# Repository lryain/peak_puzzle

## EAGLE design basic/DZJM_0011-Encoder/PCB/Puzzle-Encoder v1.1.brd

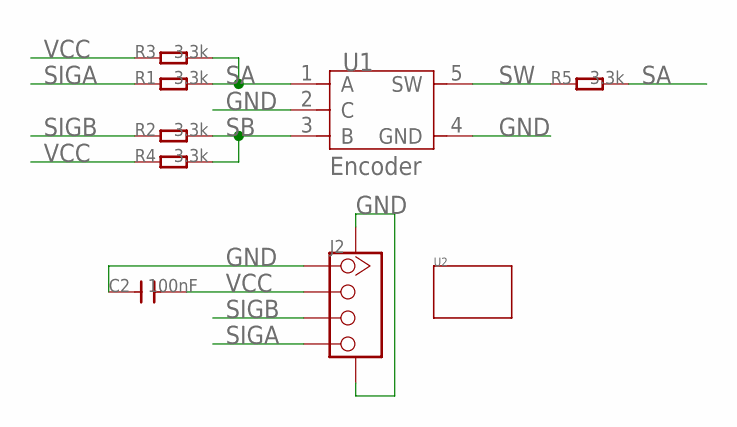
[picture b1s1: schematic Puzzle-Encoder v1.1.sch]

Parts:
C2: 100nF; C0603
J2: TWIG-4P-2.0-SMD-FEMALE-REINFORCE'DD'; 4P-SMD-2.0
R1, R2, R3, R4, R5: 3.3k; R0603
U1: Encoder; 5P-13.75X11.7X6.5H
U2: TWIG'1U'; 1U-DIM-W/-DRILL

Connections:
GND: C2.1, J2.1, J2.SS1, J2.SS2, U1.2 (C), U1.4 (GND)
SA: R1.2, R3.2, R5.2, U1.1 (A)
SB: R2.2, R4.2, U1.3 (B)
SIGA: J2.4, R1.1
SIGB: J2.3, R2.1
SW: R5.1, U1.5 (SW)
VCC: C2.2, J2.2, R3.1, R4.1

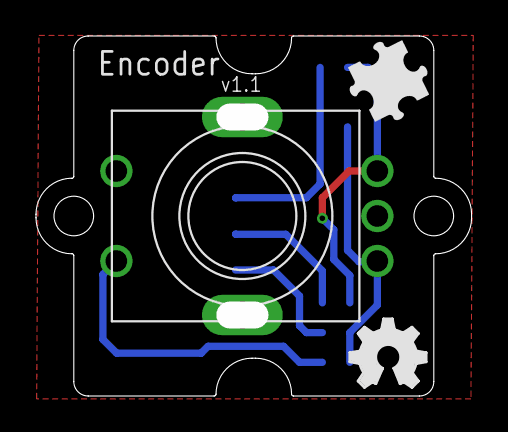
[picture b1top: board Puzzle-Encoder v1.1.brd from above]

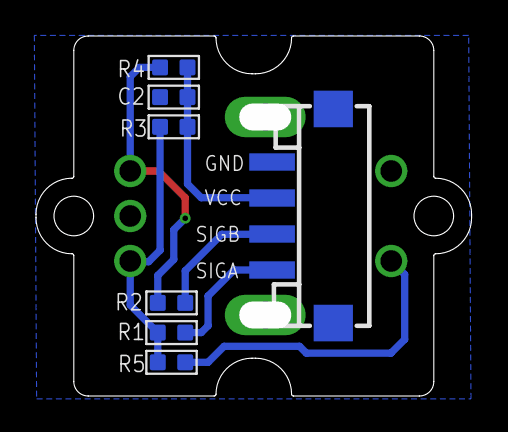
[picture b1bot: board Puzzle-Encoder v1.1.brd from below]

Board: 2 copper layers, 24.2 x 20.0 mm, 11 parts (7 on the bottom side), 7 nets.

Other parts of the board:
U$1: BRICK-LOGO-MIL-0.5
U$2: OSHW_FILLX150_NOTEXT

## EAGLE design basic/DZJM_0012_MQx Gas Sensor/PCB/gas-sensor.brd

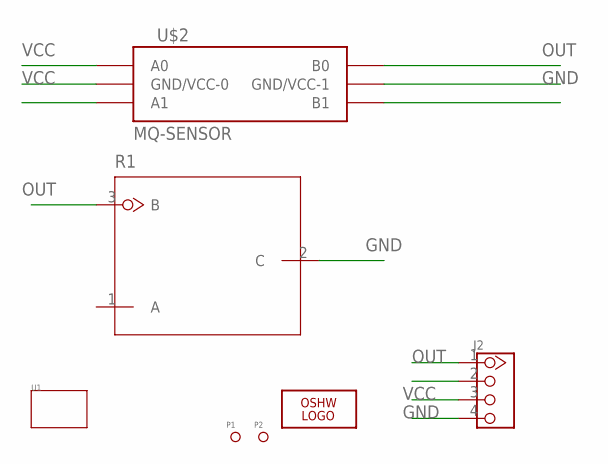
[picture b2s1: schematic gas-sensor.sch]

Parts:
J2: TWIG-2.0-LEADED; 4P-LEADED-2.0
LOGO1: LOGO-OSHW-FILLX0150-NT; OSHW_FILLX150_NOTEXT
P1, P2: PAD-MARK; ROUND-MARK-0.635
R1: DEVICE_RESISTANCE; PACKAGE__RESISTANCE
U1: TWIG-2U; 2U-DIM-W/-DRILL
U$2: MQ-SENSOR; MQ-BASE

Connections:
GND: J2.4, R1.2 (C), U$2.HB (GND/VCC-1)
OUT: J2.1, R1.3 (B), U$2.B1 (B0)
VCC: J2.3, U$2.A1 (A0), U$2.HA (GND/VCC-0)

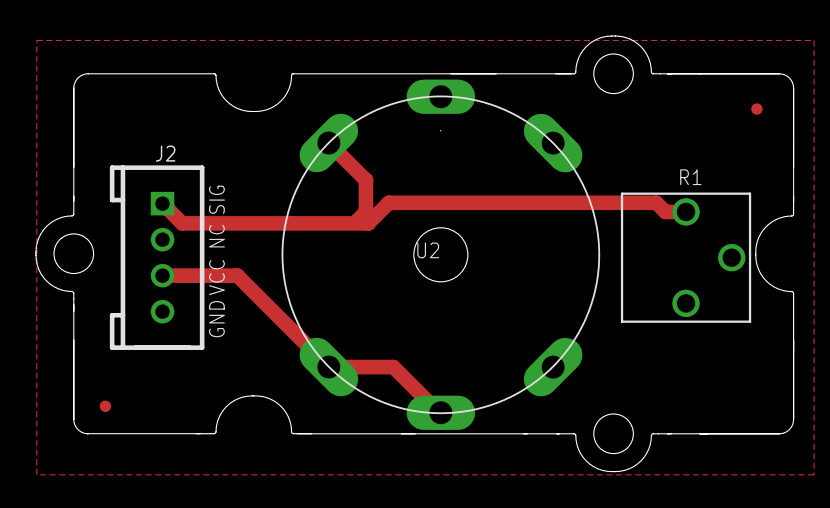
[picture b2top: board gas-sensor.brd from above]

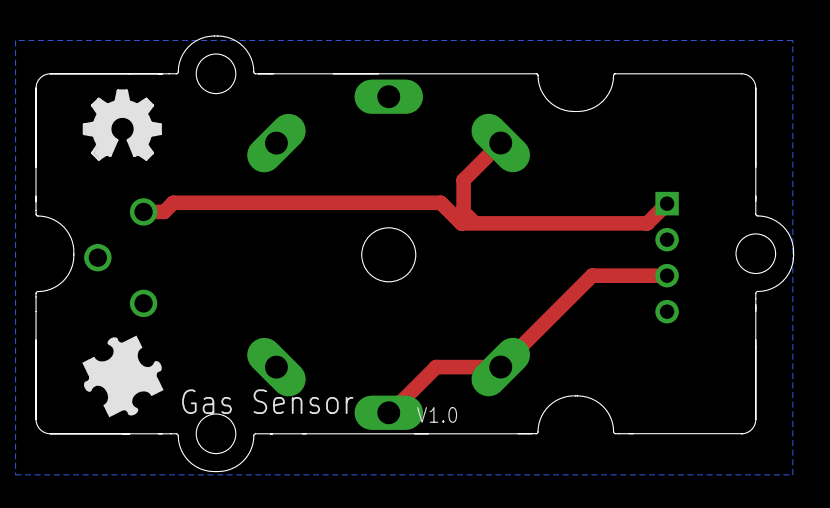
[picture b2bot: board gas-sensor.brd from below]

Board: 2 copper layers, 42.1 x 24.2 mm, 8 parts (2 on the bottom side), 3 nets.

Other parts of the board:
U$1: BRICK-LOGO-MIL-0.5

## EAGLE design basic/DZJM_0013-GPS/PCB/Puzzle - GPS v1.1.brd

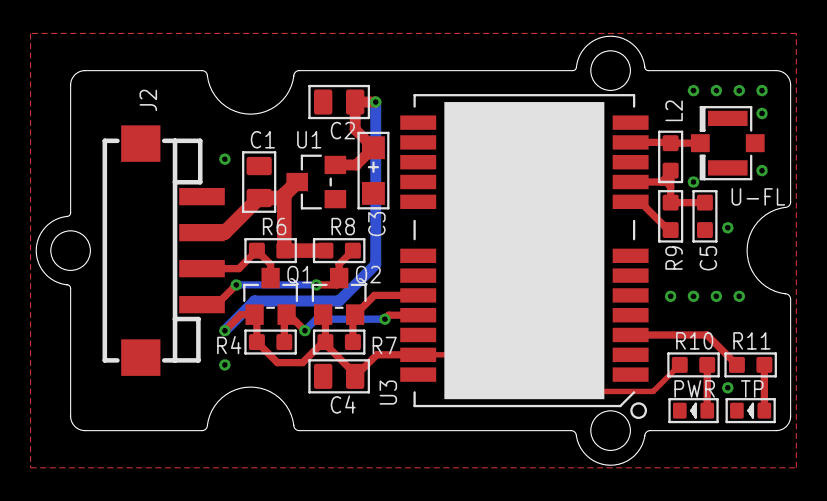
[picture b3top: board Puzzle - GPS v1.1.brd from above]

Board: 2 copper layers, 41.9 x 23.8 mm, 24 parts (1 on the bottom side), 13 nets.

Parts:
C1, C2, C4: 10uF; C0805
C3: DNP; AVX-A
C5: 100nF; C0603
J2: 4P-SMD-2.0
L2: 33nH; L0603
PWR: GREEN; LED-0603
Q1, Q2: BSN20; SOT23
R4, R6, R7, R8: 10k; R0603
R9: 0R; R0603
R10, R11: 330; R0603
TP: DNP; LED-0603
U1: XC6206P332MR-G; SOT23
U3: NEO-6M; 28P-1.1-16.0X12.2
U4: U.FL
U$1: 2U-DIM-W/DRILL
U$2: OSHW_FILLX200_NOTEXT
U$4: BRICK-LOGO-2-B-MIL-0.6

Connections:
3V3: C2.2, C3.+, C4.2, Q1.1, Q2.1, R4.2, R7.2, R10.1, U1.2, U3.23
GND: C1.1, C2.1, C3.-, C4.1, C5.2, J2.4, J2.SS1, J2.SS2, PWR.-, TP.-, U1.1, U3.7, U3.10, U3.12, U3.13, U3.22, U3.24, U4.P$1, U4.P$2
GPS_RX: Q1.2, R4.1, U3.21
GPS_TX: Q2.2, R7.1, U3.20
unnamed: L2.1, U3.11, U4.P$3
unnamed: C5.1, L2.2, R9.1, U3.9
unnamed: PWR.+, R10.2
unnamed: R9.2, U3.8
unnamed: R11.2, TP.+
RX_H: J2.2, Q1.3, R6.1
TP: R11.1, U3.3
TX_H: J2.1, Q2.3, R8.1
VCC: C1.2, J2.3, R6.2, R8.2, U1.3

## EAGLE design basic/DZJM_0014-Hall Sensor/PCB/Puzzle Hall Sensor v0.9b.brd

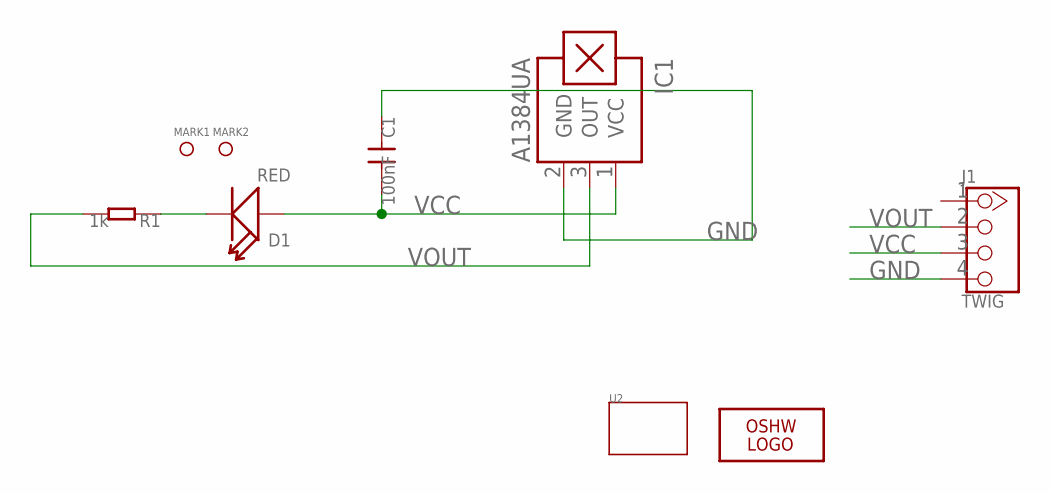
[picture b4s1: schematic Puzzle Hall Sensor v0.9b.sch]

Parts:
C1: 100nF; 0603
D1: RED; D0603
IC1: A1384UA; SIP3-UA
J1: TWIG; 4P-LEADED-2.0
LOGO1: LOGO-OSHW-FILLX0150-NT; OSHW_FILLX150_NOTEXT
MARK1, MARK2: PAD-MARK; ROUND-MARK-0.635
R1: 1k; 0603
U2: TWIG-1U; 1U-DIM-W/-DRILL

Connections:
GND: C1.1, IC1.2 (GND), J1.4
unnamed: D1.-, R1.1
VCC: C1.2, D1.+, IC1.1 (VCC), J1.3
VOUT: IC1.3 (OUT), J1.2, R1.2

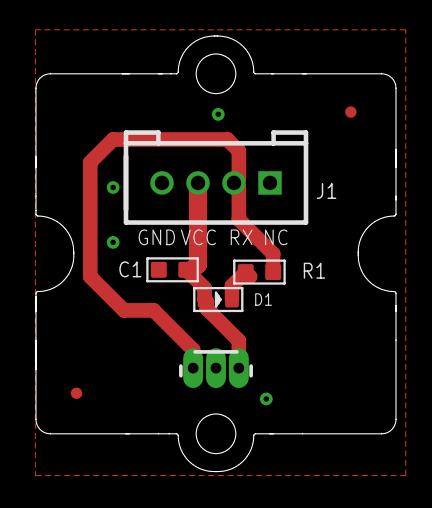
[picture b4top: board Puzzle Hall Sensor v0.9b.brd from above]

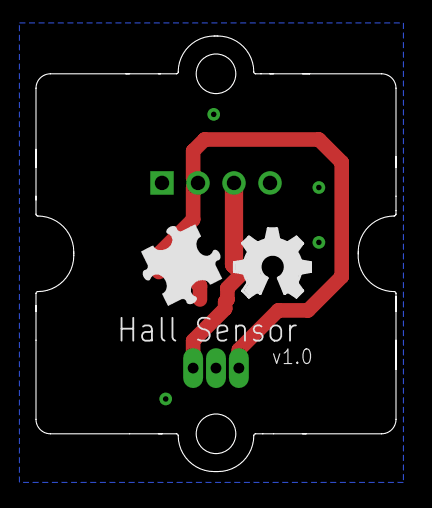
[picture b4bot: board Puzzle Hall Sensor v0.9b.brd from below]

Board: 2 copper layers, 20.0 x 24.2 mm, 10 parts (2 on the bottom side), 4 nets.

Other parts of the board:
U$1: BRICK-LOGO-MIL-0.5

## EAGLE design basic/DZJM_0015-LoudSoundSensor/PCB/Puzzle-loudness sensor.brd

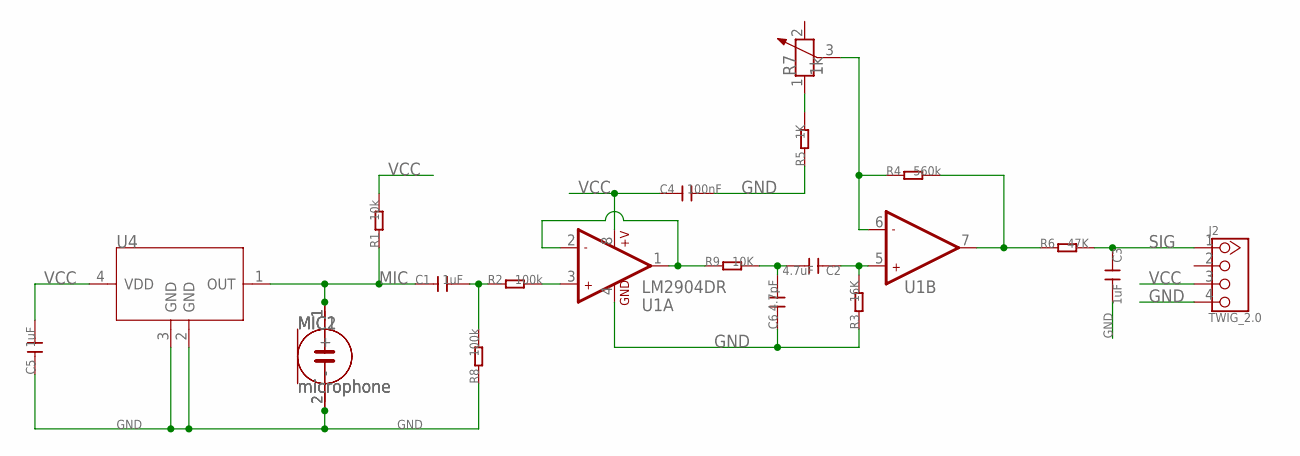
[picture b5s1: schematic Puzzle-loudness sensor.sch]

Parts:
C1, C3, C5: 1uF; C0603
C2: 4.7uF; C0805
C4: 100nF; C0603
C6: 4.7pF; C0603
J2: TWIG_2.0; 2.0_1X4
MIC1, MIC2: microphone; 2P-D8.9MM
R1: 10k; R0603
R2, R8: 100k; R0603
R3: 16K; R0603
R4: 560k; R0603
R5: 1K; R0603
R6: 47K; R0603
R7: 1k; 3P-SQUA-7X6.8
R9: 10K; R0603
U1: LM2904DR; SO08
U4: SENSOR-MULPS4CX; 4P-SMD-2.95X3.76X1.1H

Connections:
GND: C3.2, C4.2, C5.1, C6.1, J2.4, MIC1.2 (-), MIC2.2 (-), R3.1, R5.1, R8.1, U1.4 (GND), U4.2 (GND), U4.3 (GND)
MIC: C1.1, MIC1.1 (+), MIC2.1 (+), R1.1, U4.1 (OUT)
unnamed: R2.2, U1.3 (+IN1)
unnamed: C1.2, R2.1, R8.2
unnamed: R9.1, U1.1 (OUT1), U1.2 (-IN1)
unnamed: C2.1, R3.2, U1.5 (+IN2)
unnamed: R4.1, R7.3, U1.6 (-IN2)
unnamed: R4.2, R6.1, U1.7 (OUT2)
unnamed: R5.2, R7.1
unnamed: C2.2, C6.2, R9.2
SIG: C3.1, J2.1, R6.2
VCC: C4.1, C5.2, J2.3, R1.2, U1.8 (+V), U4.4 (VDD)

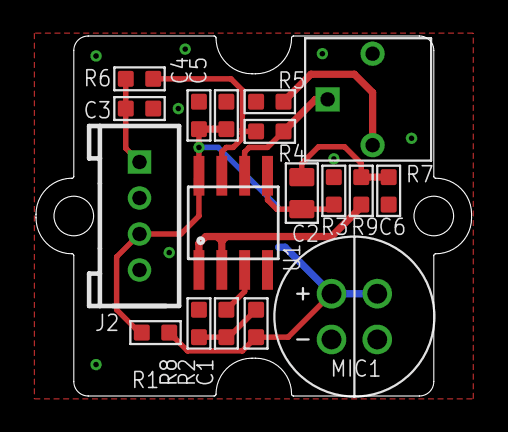
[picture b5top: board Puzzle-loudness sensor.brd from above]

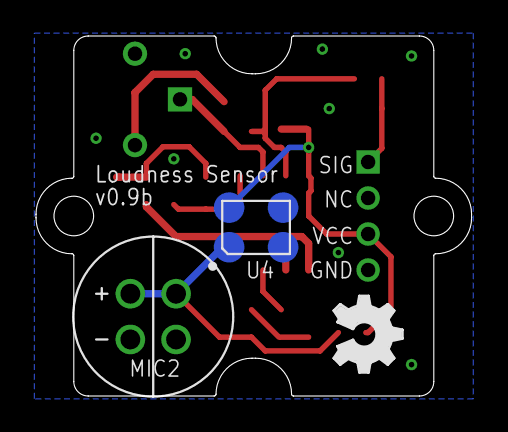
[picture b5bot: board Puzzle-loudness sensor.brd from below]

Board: 2 copper layers, 24.2 x 20.0 mm, 22 parts (3 on the bottom side), 12 nets.

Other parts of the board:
U$1: OSHW_FILLX150_NOTEXT
U$2: 1U-DIM-W/-DRILL

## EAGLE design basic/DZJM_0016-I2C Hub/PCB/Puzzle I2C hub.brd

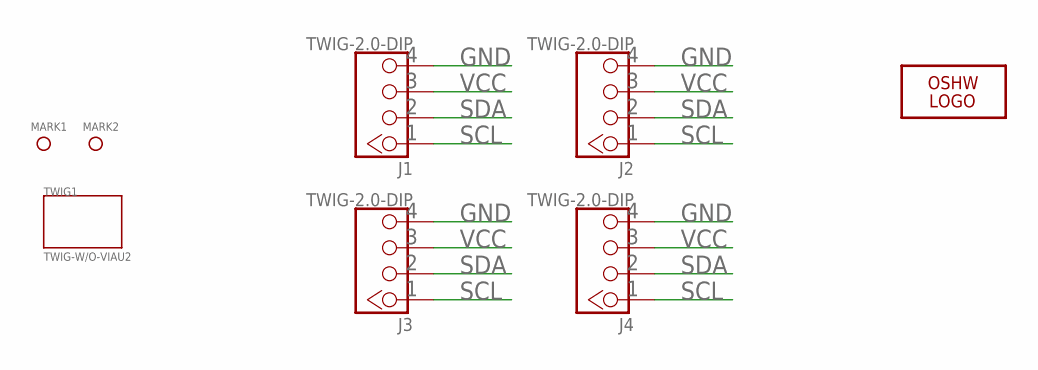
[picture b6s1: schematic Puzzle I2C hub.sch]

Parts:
J1, J2, J3, J4: TWIG-2.0-DIP; 2.0_1X4
LOGO3: LOGO-OSHW-FILLX0150-NT; OSHW_FILLX150_NOTEXT
MARK1, MARK2: PAD-MARK; MARK
TWIG1: TWIG-W/O-VIAU2; U2N

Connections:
GND: J1.4, J2.4, J3.4, J4.4
SCL: J1.1, J2.1, J3.1, J4.1
SDA: J1.2, J2.2, J3.2, J4.2
VCC: J1.3, J2.3, J3.3, J4.3

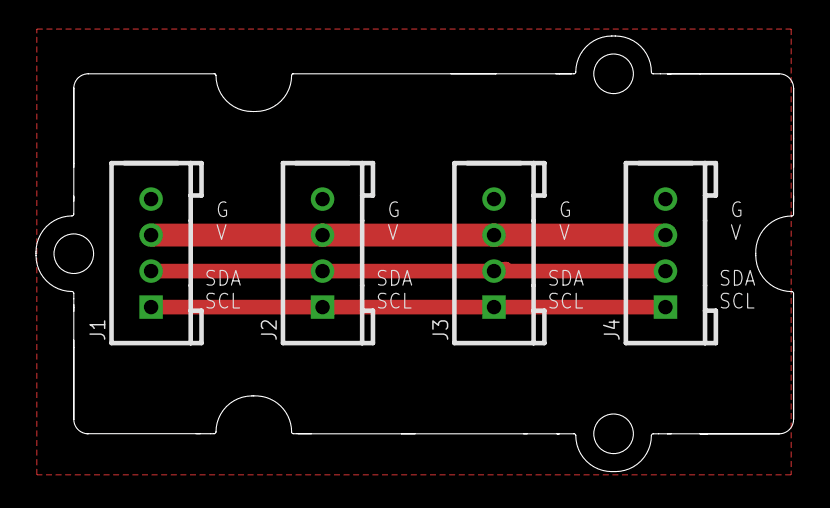
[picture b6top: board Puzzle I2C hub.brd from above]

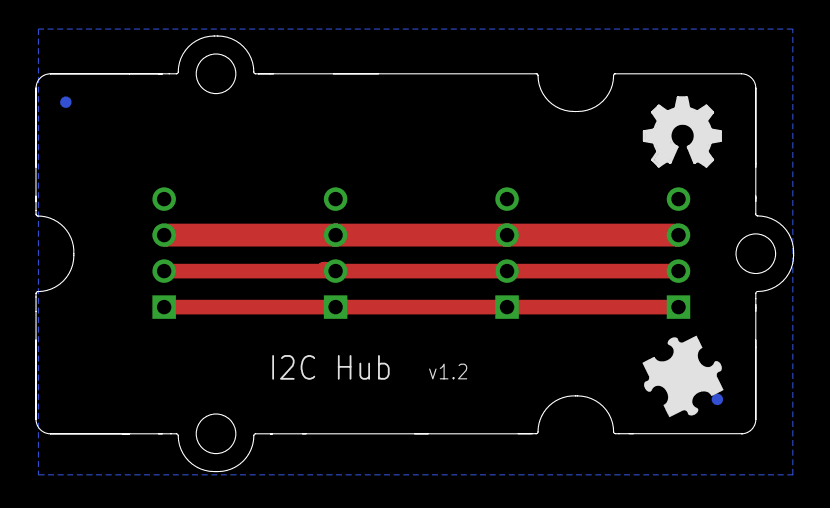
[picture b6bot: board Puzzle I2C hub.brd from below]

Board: 2 copper layers, 42.1 x 24.2 mm, 9 parts (4 on the bottom side), 4 nets.

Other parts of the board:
U$2: BRICK-LOGO-MIL-0.5

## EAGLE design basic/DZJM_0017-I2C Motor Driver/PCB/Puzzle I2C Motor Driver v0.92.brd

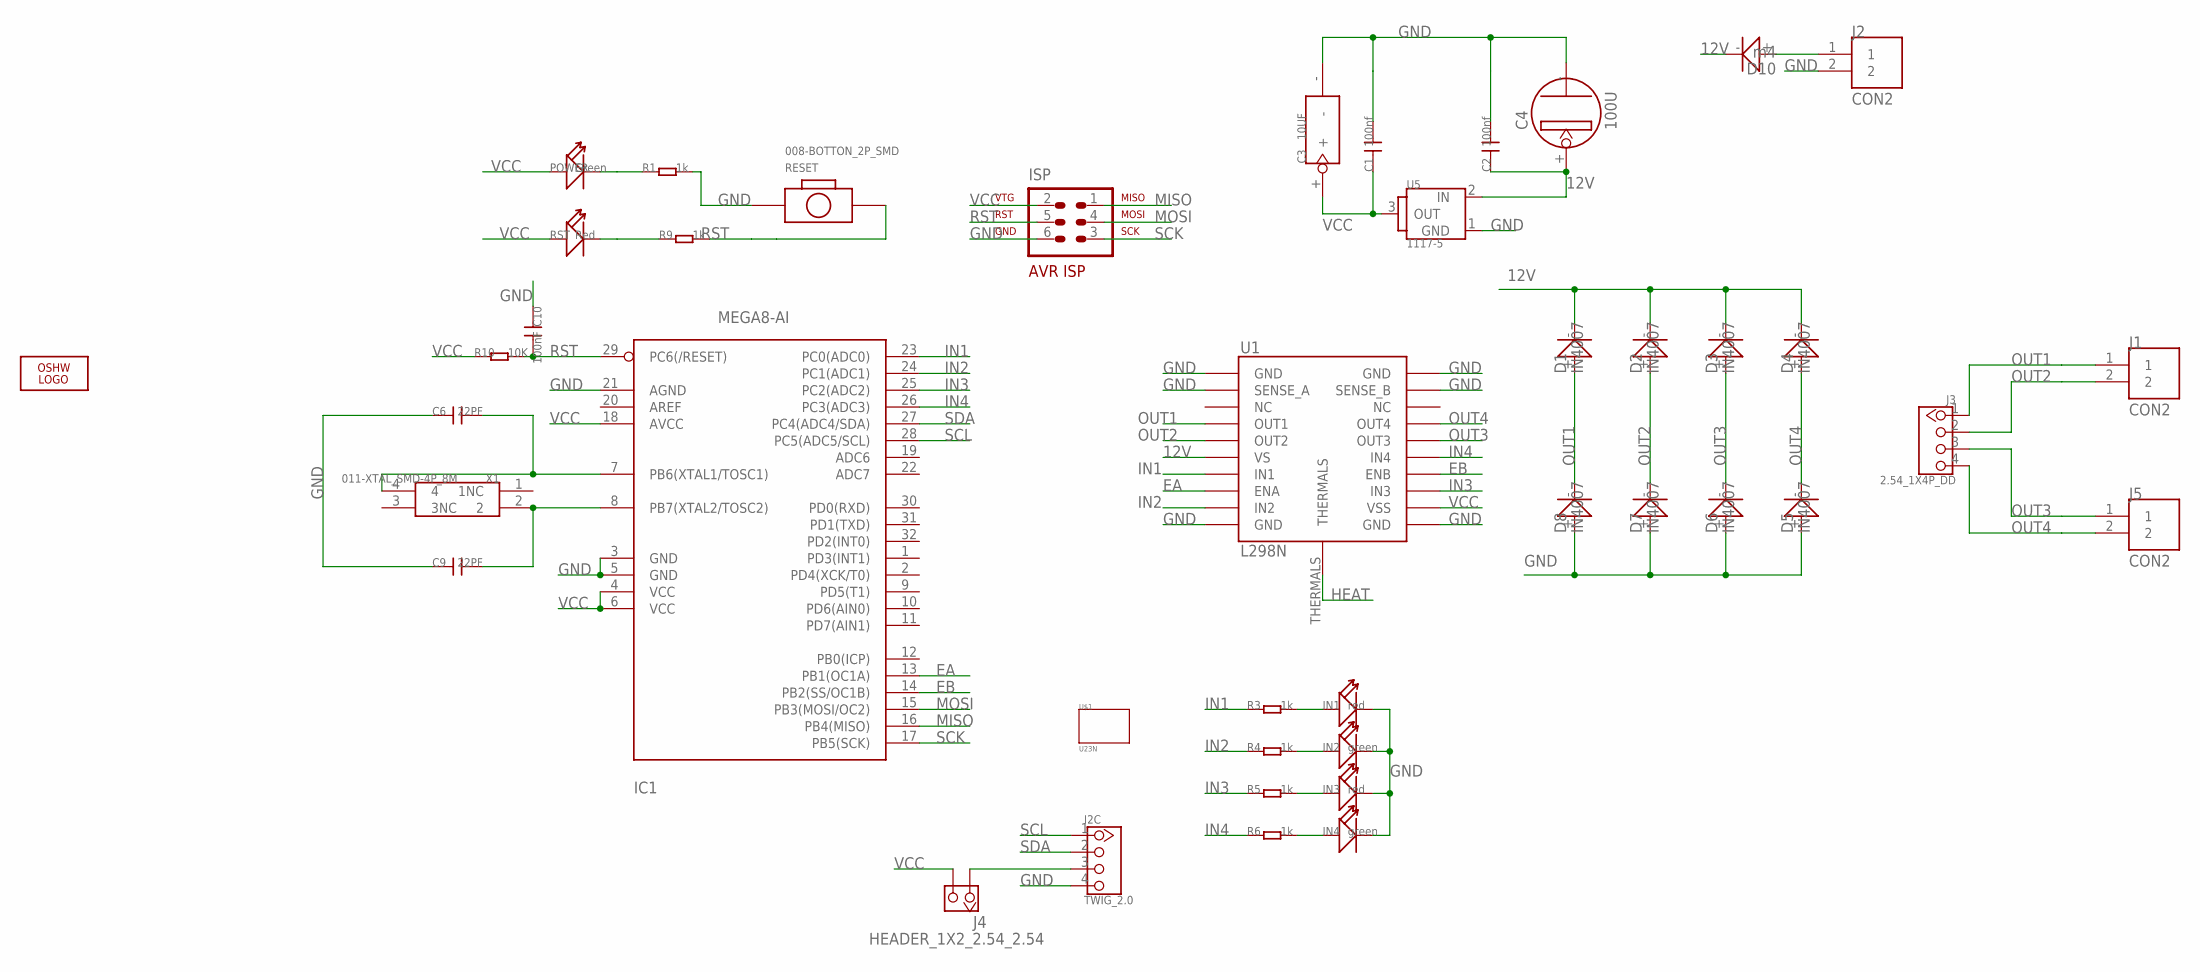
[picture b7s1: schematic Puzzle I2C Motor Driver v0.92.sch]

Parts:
C1, C2: 100nf; 0603_S
C3: 10UF; C_TAN_3X3.5
C4: 100U; SANYO-OSCON_SMD_C6
C6, C9: 22PF; 0603_S
C10: 100nF; 0603_S
D1, D2, D3, D4, D5, D6, D7, D8: IN4007; D2010
D10: m4; D2010
I2C: TWIG_2.0; 2.0_1X4
IC1: MEGA8-AI; TQFP32-08
IN1, IN3: red; D0603
IN2, IN4: green; D0603
ISP: AVR-ISP-6
J1, J2, J5: CON2
J3: 2.54_1X4P_DD; CK_1X4
J4: HEADER_1X2_2.54_2.54; 65*35
LOGO2: LOGO-OSHW-FILLX0200-NT; OSHW_FILLX200_NOTEXT
POWER: Green; D0603
R1, R3, R4, R5, R6, R9: 1k; 0603-1
R10: 10K; 0603-1
RESET: 008-BOTTON_2P_SMD; BOTTON_1
RST: Red; D0603
U1: L298N; POWERSO20
U5: 1117-5; TO252
U$1: U23N; U2*3N
X1: 011-XTAL_SMD-4P_8M; CRYSTAL-SMD-5X3

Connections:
12V: C2.1, C4.+, D1.-, D2.-, D3.-, D4.-, D10.-, U1.P$6 (VS), U5.2 (IN)
EA: IC1.13 (PB1(OC1A)), U1.P$8 (ENA)
EB: IC1.14 (PB2(SS/OC1B)), U1.P$14 (ENB)
GND: C1.2, C2.2, C3.-, C4.-, C6.1, C9.1, C10.1, D5.+, D6.+, D7.+, D8.+, I2C.4, IC1.3 (GND), IC1.5 (GND), IC1.21 (AGND), IN1.-, IN2.-, IN3.-, IN4.-, ISP.6, J2.2, R1.2, RESET.1, U1.P$1 (GND), U1.P$2 (SENSE_A), U1.P$10 (GND), U1.P$11 (GND), U1.P$19 (SENSE_B), U1.P$20 (GND), U5.1 (GND)
HEAT: U1.THERMALS
IN1: IC1.23 (PC0(ADC0)), R3.1, U1.P$7 (IN1)
IN2: IC1.24 (PC1(ADC1)), R4.1, U1.P$9 (IN2)
IN3: IC1.25 (PC2(ADC2)), R5.1, U1.P$13 (IN3)
IN4: IC1.26 (PC3(ADC3)), R6.1, U1.P$15 (IN4)
MISO: IC1.16 (PB4(MISO)), ISP.1
MOSI: IC1.15 (PB3(MOSI/OC2)), ISP.4
unnamed: IN3.+, R5.2
unnamed: I2C.3, J4.1
unnamed: POWER.-, R1.1
unnamed: D10.+, J2.1
unnamed: C6.2, IC1.7 (PB6(XTAL1/TOSC1)), X1.4
unnamed: C9.2, IC1.8 (PB7(XTAL2/TOSC2)), X1.2
unnamed: R9.1, RST.-
unnamed: IN1.+, R3.2
unnamed: IN2.+, R4.2
unnamed: IN4.+, R6.2
OUT1: D1.+, D8.-, J1.1, J3.1, U1.P$4 (OUT1)
OUT2: D2.+, D7.-, J1.2, J3.2, U1.P$5 (OUT2)
OUT3: D3.+, D6.-, J3.3, J5.1, U1.P$16 (OUT3)
OUT4: D4.+, D5.-, J3.4, J5.2, U1.P$17 (OUT4)
RST: C10.2, IC1.29 (PC6(/RESET)), ISP.5, R9.2, R10.2, RESET.P$2 (2)
SCK: IC1.17 (PB5(SCK)), ISP.3
SCL: I2C.1, IC1.28 (PC5(ADC5/SCL))
SDA: I2C.2, IC1.27 (PC4(ADC4/SDA))
VCC: C1.1, C3.+, IC1.4 (VCC), IC1.6 (VCC), IC1.18 (AVCC), ISP.2, J4.2, POWER.+, R10.1, RST.+, U1.P$12 (VSS), U5.3 (OUT)

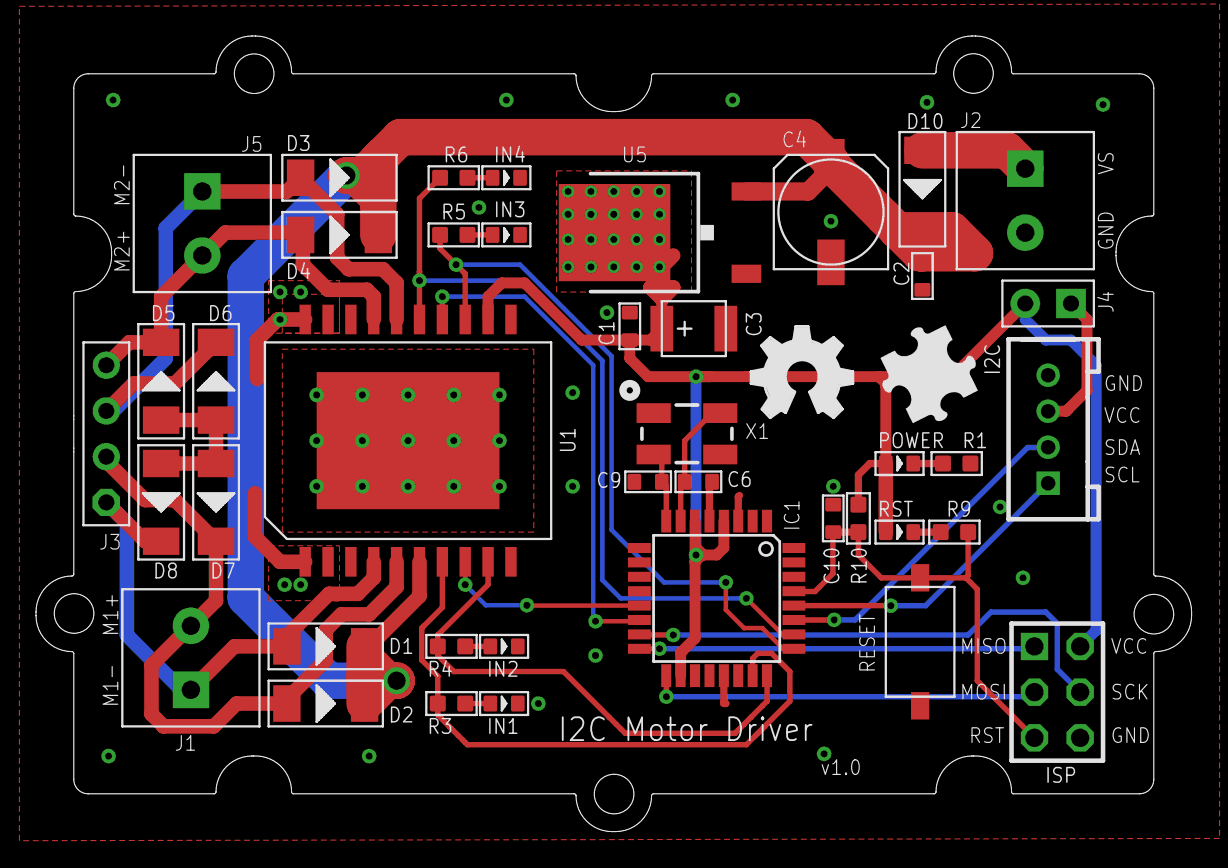
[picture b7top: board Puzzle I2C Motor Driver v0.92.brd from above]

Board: 2 copper layers, 64.2 x 44.2 mm, 44 parts (0 on the bottom side), 29 nets.

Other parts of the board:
U$3: BRICK-LOGO-MIL-0.6

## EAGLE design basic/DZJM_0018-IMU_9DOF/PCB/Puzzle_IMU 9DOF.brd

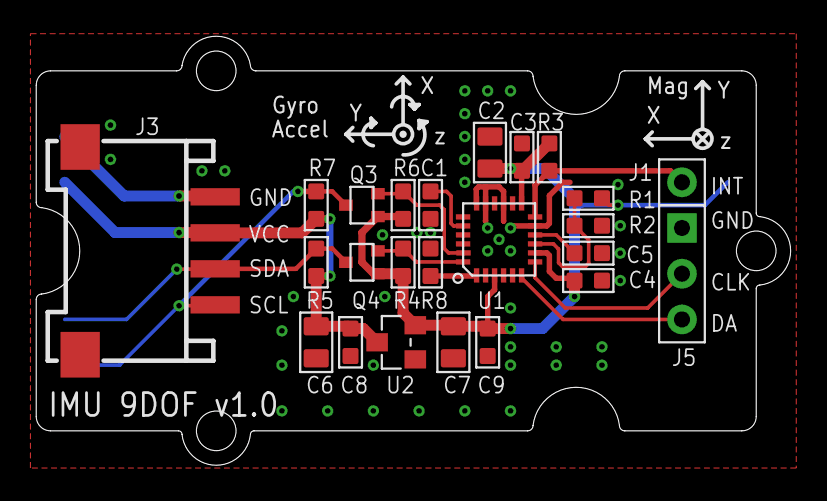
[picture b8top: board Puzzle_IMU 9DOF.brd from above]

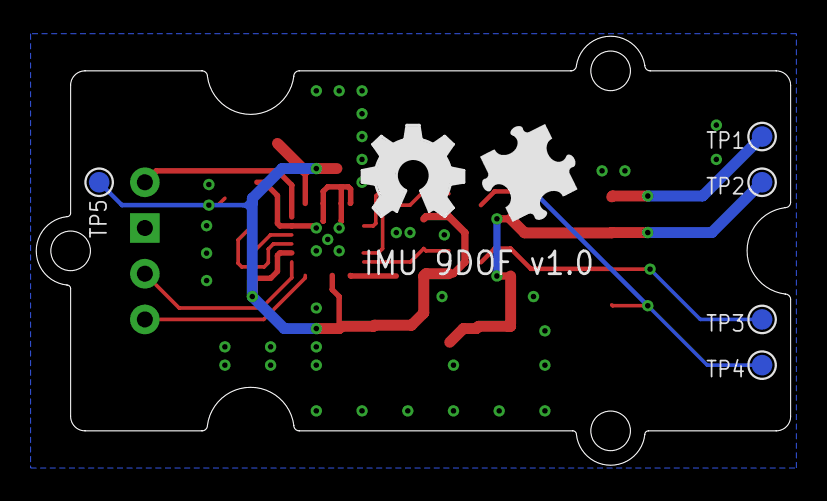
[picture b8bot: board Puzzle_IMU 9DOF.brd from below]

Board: 2 copper layers, 41.9 x 23.8 mm, 32 parts (7 on the bottom side), 14 nets.

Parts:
C1: 2.2nF; C0603
C2, C6, C7: 10uF; C0805
C3, C5, C8, C9: 100nF; C0603
C4: 10nF; C0603
J1: DNP; 1P-65/35MIL
J3: 4P-SMD-2.0-90D
J5: DNP; 3P-2.54
Q3, Q4: 2N7002KW; SOT323
R1: DNP; R0603
R2, R3: 10k; R0603
R4, R5, R6, R7: 4.7k; R0603
R8: 0R; R0603
TP1, TP2, TP3, TP4, TP5: TP_4545
U1: MPU-9150; LGA-24
U2: XC6206P302; SOT23
U3: GROVE-TEST-PLATFORM
U$3: OSHW_FILLX200_NOTEXT
U$13: BRICK-LOGO-MIL-0.6

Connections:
ES_CLK: J5.2, U1.7
ES_DA: J5.3, U1.6
GND: C1.1, C2.1, C3.1, C4.1, C5.1, C6.1, C7.1, C8.1, C9.1, J3.4, J3.SS1, J3.SS2, J5.1, R8.1, TP1.T, U1.11, U1.15, U1.17, U1.18, U2.1
INT: J1.1, R3.1, U1.12
unnamed: R1.1, R2.2, U1.9
unnamed: C1.2, U1.20
unnamed: R8.2, U1.1
unnamed: C5.2, U1.10
SCL_H: J3.1, Q3.3, R7.1, TP4.T
SCL_L: Q3.2, R6.1, U1.23
SDA_H: J3.2, Q4.3, R5.1, TP3.T
SDA_L: Q4.2, R4.1, U1.24
VCC: C6.2, C8.2, J3.3, R5.2, R7.2, TP2.T, U2.3
VCC_3V3: C2.2, C3.2, C4.2, C7.2, C9.2, Q3.1, Q4.1, R1.2, R3.2, R4.2, R6.2, TP5.T, U1.3, U1.8, U1.13, U2.2

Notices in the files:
parts and their libraries:
SparkFun-Connectors: Licensing: CC v3.0 Share-Alike You are welcome to use this library for commercial purposes.
